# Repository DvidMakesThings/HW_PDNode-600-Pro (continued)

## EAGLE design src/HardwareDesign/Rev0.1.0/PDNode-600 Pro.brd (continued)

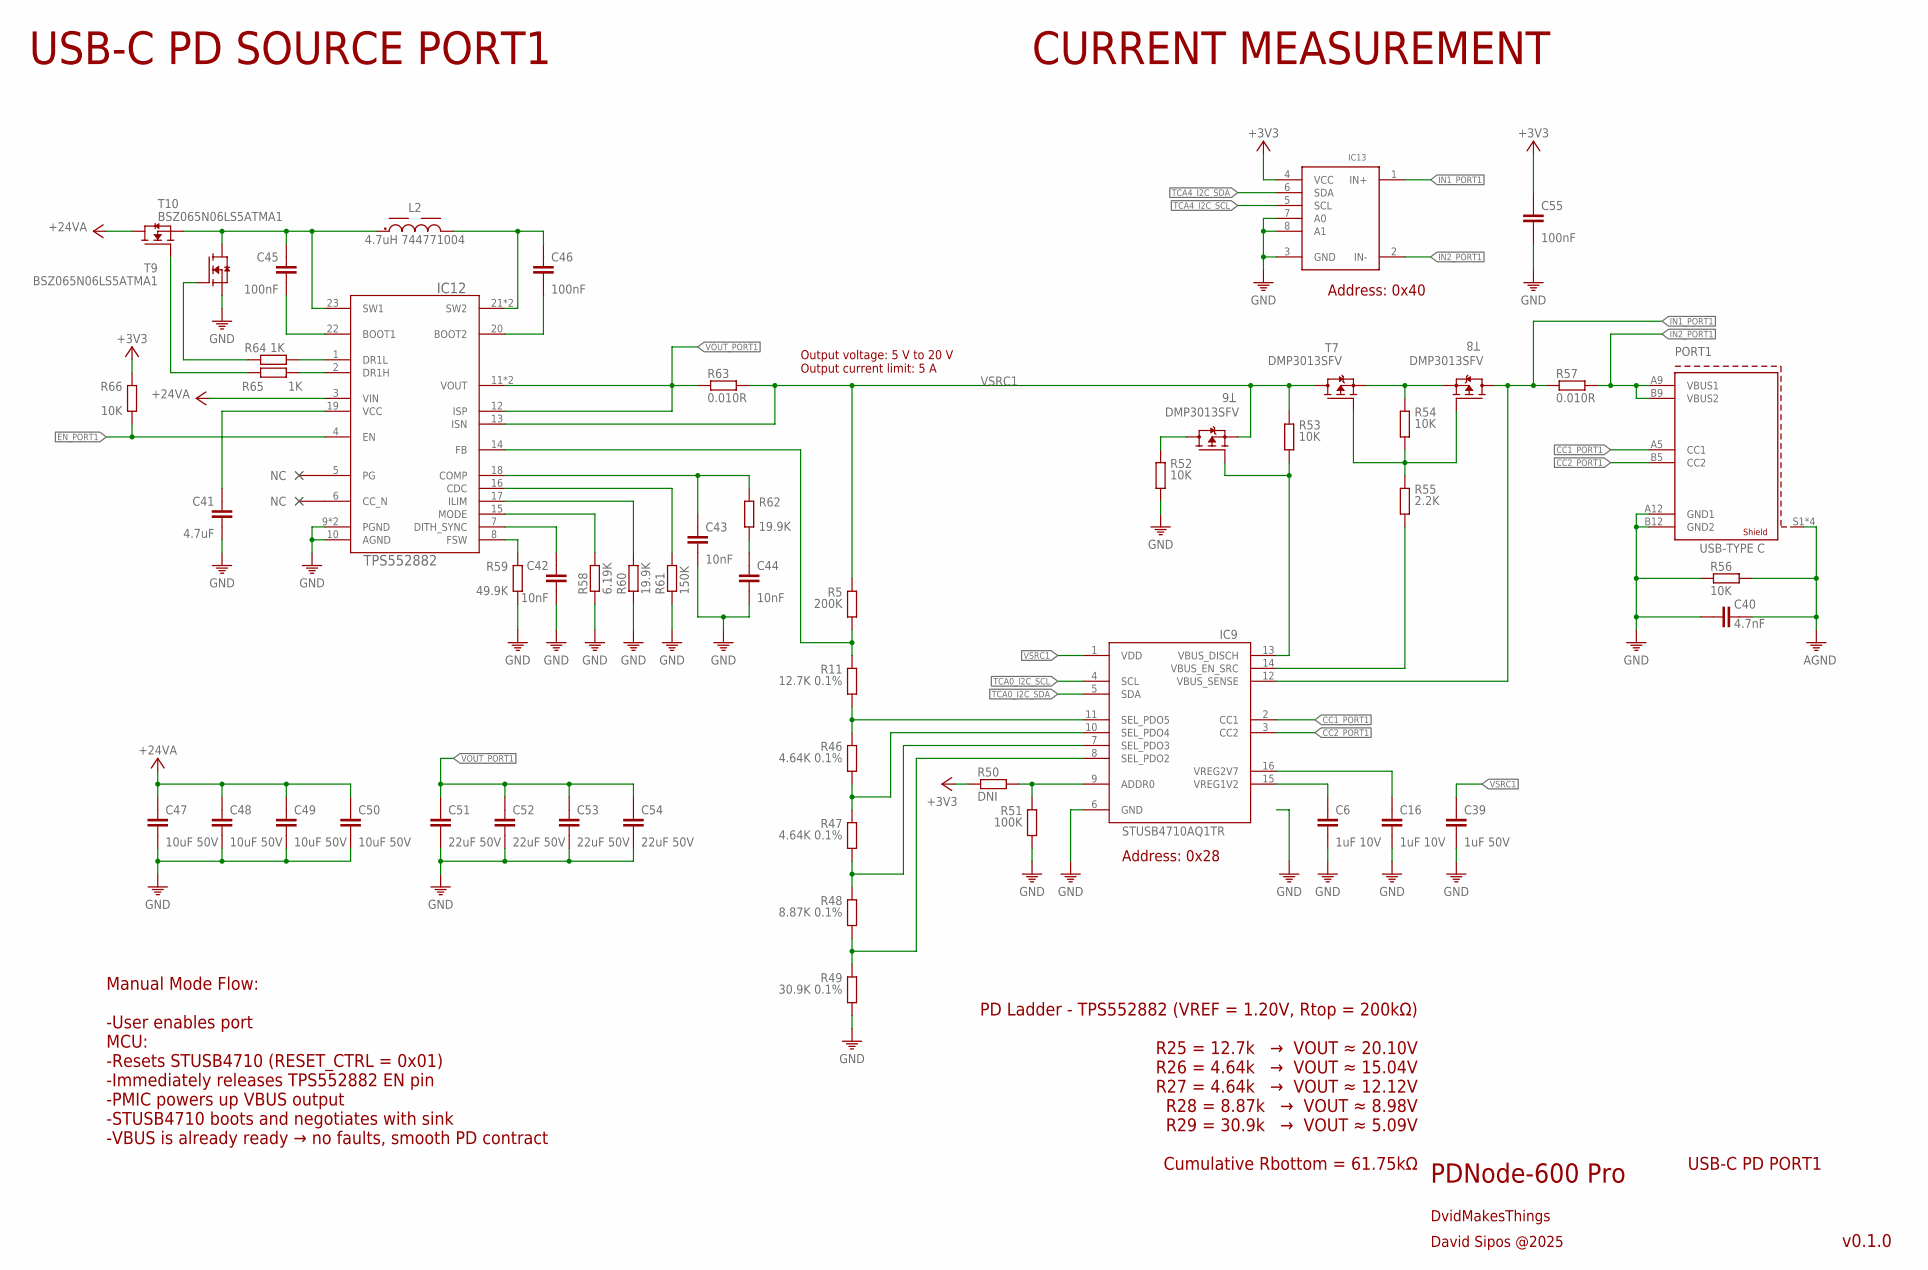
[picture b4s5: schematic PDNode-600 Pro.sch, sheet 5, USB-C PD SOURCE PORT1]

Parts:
C6, C16: 1uF 10V; 0201
C39: 1uF 50V; C0603
C40: 4.7nF; C0402
C41: 4.7uF; C0402
C42, C43, C44: 10nF; 0201
C45, C46: 100nF; C0402
C47, C48, C49, C50: 10uF 50V; C0805
C51, C52, C53, C54: 22uF 50V; C0805
C55: 100nF; 0201
IC9: STUSB4710AQ1TR; QFN50P300X300X55-16N
IC12: TPS552882; RPM0026A-MFG
IC13: INA219BIDCNT; SOT23-8
L2: 4.7uH 744771004; WE-PD_1280
PORT1: 632722100213
R5: 200K; R0201
R11: 12.7K 0.1%; R0201
R46, R47: 4.64K 0.1%; R0201
R48: 8.87K 0.1%; R0201
R49: 30.9K 0.1%; R0201
R50: DNI; R0201
R51: 100K; R0201
R52, R53, R56: 10K; 0402
R54, R66: 10K; R0201
R55: 2.2K; R0201
R57, R63: 0.010R; 2512
R58: 6.19K; R0201
R59: 49.9K; R0201
R60, R62: 19.9K; R0201
R61: 150K; R0201
R64, R65: 1K; R0201
T6, T7, T8: DMP3013SFV; POWERDI3333-8_UX_DIO-L
T9, T10: BSZ065N06LS5ATMA1; POWERDI3333-8_UX_DIO-L

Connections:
+3V3: C55.1, IC13.4 (VCC), R50.1, R66.1; also elsewhere on the board
+24V_A: C47.1, C48.1, C49.1, C50.1, IC12.3 (VIN), T10.5 (D), T10.6 (D), T10.7 (D), T10.8 (D), T10.9 (D); also elsewhere on the board
AGND: C40.2, PORT1.S1 (SHIELD1), PORT1.S2 (SHIELD1), PORT1.S3 (SHIELD1), PORT1.S4 (SHIELD1), R56.2; also elsewhere on the board
CC1_PORT1: IC9.2 (CC1), PORT1.A5 (CC1)
CC2_PORT1: IC9.3 (CC2), PORT1.B5 (CC2)
EN_PORT1: IC12.4 (EN), R66.2; also elsewhere on the board
GND: C6.2, C16.2, C39.2, C40.1, C41.2, C42.2, C43.2, C44.2, C47.2, C48.2, C49.2, C50.2, C51.2, C52.2, C53.2, C54.2, C55.2, IC9.6 (GND), IC12.9 (PGND), IC12.10 (AGND), IC12.24 (PGND), IC13.3 (GND), IC13.7 (A0), IC13.8 (A1), PORT1.A12 (GND1), PORT1.B12 (GND2), R49.2, R51.2, R52.2, R56.1, R58.2, R59.2, R60.2, R61.2, T9.1 (S), T9.2 (S), T9.3 (S); also elsewhere on the board
IN1_PORT1: IC9.12 (VBUS_SENSE), IC13.1 (IN+), R57.1, T8.5 (D), T8.6 (D), T8.7 (D), T8.8 (D), T8.9 (D)
IN2_PORT1: IC13.2 (IN-), PORT1.A9 (VBUS1), PORT1.B9 (VBUS2), R57.2
unnamed: IC12.14 (FB), R5.2, R11.1
unnamed: IC9.11 (SEL_PDO5), R11.2, R46.1
unnamed: IC9.10 (SEL_PDO4), R46.2, R47.1
unnamed: IC9.7 (SEL_PDO3), R47.2, R48.1
unnamed: IC9.8 (SEL_PDO2), R48.2, R49.1
unnamed: C6.1, IC9.15 (VREG1V2)
unnamed: C16.1, IC9.16 (VREG2V7)
unnamed: IC9.9 (ADDR0), R50.2, R51.1
unnamed: R52.1, T6.5 (D), T6.6 (D), T6.7 (D), T6.8 (D), T6.9 (D)
unnamed: IC9.13 (VBUS_DISCH), R53.2, T6.4 (G)
unnamed: R54.1, T7.1 (S), T7.2 (S), T7.3 (S), T8.1 (S), T8.2 (S), T8.3 (S)
unnamed: R54.2, R55.1, T7.4 (G), T8.4 (G)
unnamed: IC9.14 (VBUS_EN_SRC), R55.2
unnamed: C44.1, R62.2
unnamed: IC12.8 (FSW), R59.1
unnamed: C42.1, IC12.7 (DITH_SYNC)
unnamed: IC12.15 (MODE), R58.1
unnamed: IC12.17 (ILIM), R60.1
unnamed: IC12.16 (CDC), R61.1
unnamed: C43.1, IC12.18 (COMP), R62.1
unnamed: C41.1, IC12.19 (VCC)
unnamed: C45.1, IC12.23 (SW1), L2.1, T9.5 (D), T9.6 (D), T9.7 (D), T9.8 (D), T9.9 (D), T10.1 (S), T10.2 (S), T10.3 (S)
unnamed: C46.1, IC12.21 (SW2), IC12.25 (SW2), L2.2
unnamed: C45.2, IC12.22 (BOOT1)
unnamed: C46.2, IC12.20 (BOOT2)
unnamed: R65.2, T10.4 (G)
unnamed: R64.2, T9.4 (G)
unnamed: IC12.1 (DR1L), R64.1
unnamed: IC12.2 (DR1H), R65.1
TCA0_I2C_SCL: IC9.4 (SCL); also elsewhere on the board
TCA0_I2C_SDA: IC9.5 (SDA); also elsewhere on the board
TCA4_I2C_SCL: IC13.5 (SCL); also elsewhere on the board
TCA4_I2C_SDA: IC13.6 (SDA); also elsewhere on the board
VOUT_PORT1: C51.1, C52.1, C53.1, C54.1, IC12.11 (VOUT), IC12.12 (ISP), IC12.26 (VOUT), R63.1
VSRC1: C39.1, IC9.1 (VDD), IC12.13 (ISN), R5.1, R53.1, R63.2, T6.1 (S), T6.2 (S), T6.3 (S), T7.5 (D), T7.6 (D), T7.7 (D), T7.8 (D), T7.9 (D)

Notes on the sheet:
PDNode-600 Pro
DvidMakesThings
David Sipos @2025
USB-C PD SOURCE PORT1
CURRENT MEASUREMENT
USB-C PD PORT1
v0.1.0
Manual Mode Flow: -User enables port MCU: -Resets STUSB4710 (RESET_CTRL = 0x01) -Immediately releases TPS552882 EN pin -PMIC powers up VBUS output -STUSB4710 boots and negotiates with sink -VBUS is already ready → no faults, smooth PD contract
Output voltage: 5 V to 20 V Output current limit: 5 A
PD Ladder - TPS552882 (VREF = 1.20V, Rtop = 200kΩ) R25 = 12.7k → VOUT ≈ 20.10V R26 = 4.64k → VOUT ≈ 15.04V R27 = 4.64k → VOUT ≈ 12.12V R28 = 8.87k → VOUT ≈ 8.98V R29 = 30.9k → VOUT ≈ 5.09V Cumulative Rbottom = 61.75kΩ
Address: 0x40
Address: 0x28

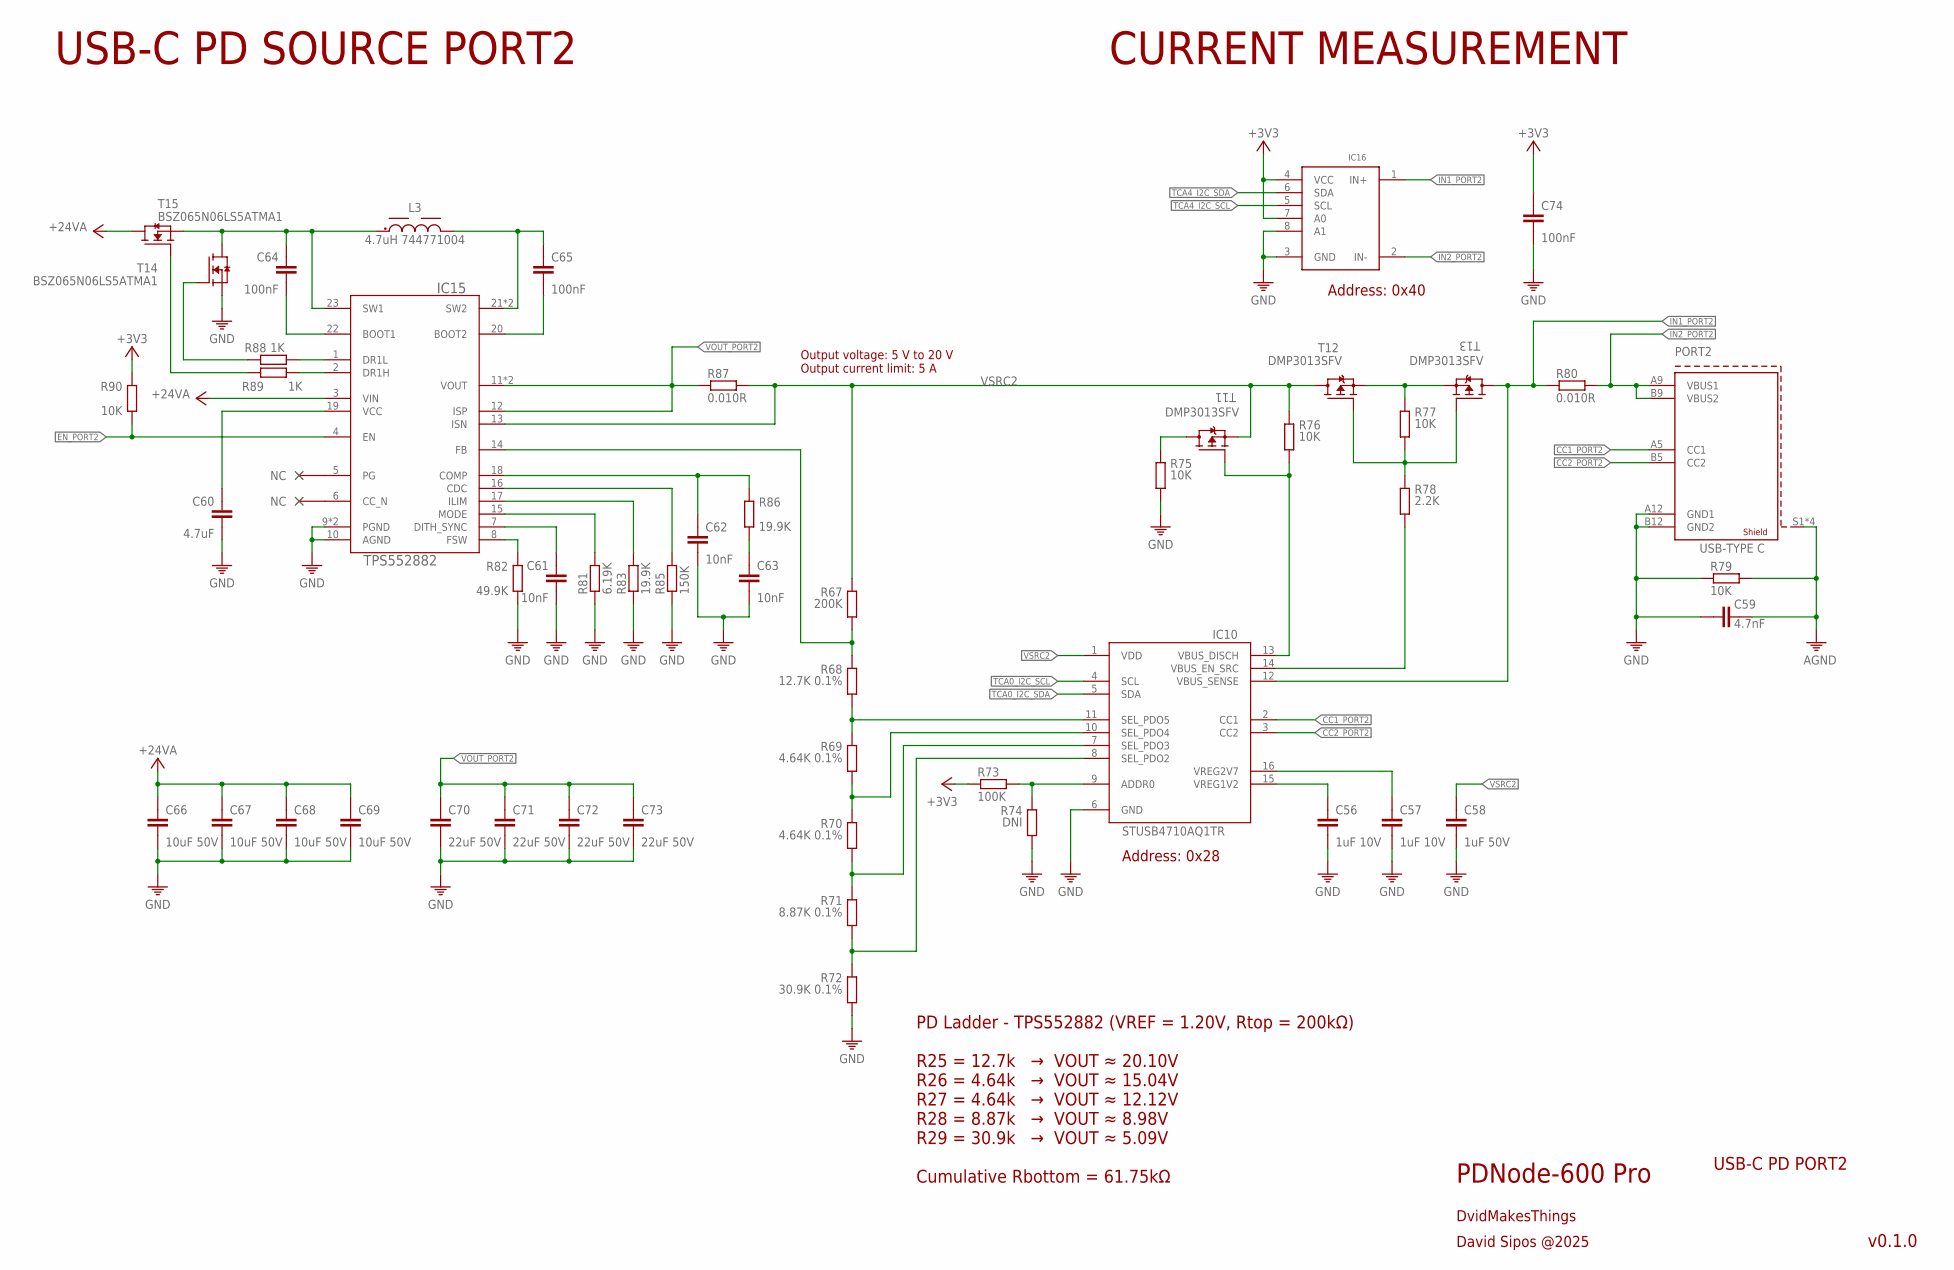
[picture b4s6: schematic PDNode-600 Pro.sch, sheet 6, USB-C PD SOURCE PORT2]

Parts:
C56, C57: 1uF 10V; 0201
C58: 1uF 50V; C0603
C59: 4.7nF; C0402
C60: 4.7uF; C0402
C61, C62, C63: 10nF; 0201
C64, C65: 100nF; C0402
C66, C67, C68, C69: 10uF 50V; C0805
C70, C71, C72, C73: 22uF 50V; C0805
C74: 100nF; 0201
IC10: STUSB4710AQ1TR; QFN50P300X300X55-16N
IC15: TPS552882; RPM0026A-MFG
IC16: INA219BIDCNT; SOT23-8
L3: 4.7uH 744771004; WE-PD_1280
PORT2: 632722100213
R67: 200K; R0201
R68: 12.7K 0.1%; R0201
R69, R70: 4.64K 0.1%; R0201
R71: 8.87K 0.1%; R0201
R72: 30.9K 0.1%; R0201
R73: 100K; R0201
R74: DNI; R0201
R75, R76, R79: 10K; 0402
R77, R90: 10K; R0201
R78: 2.2K; R0201
R80, R87: 0.010R; 2512
R81: 6.19K; R0201
R82: 49.9K; R0201
R83, R86: 19.9K; R0201
R85: 150K; R0201
R88, R89: 1K; R0201
T11, T12, T13: DMP3013SFV; POWERDI3333-8_UX_DIO-L
T14, T15: BSZ065N06LS5ATMA1; POWERDI3333-8_UX_DIO-L

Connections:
+3V3: C74.1, IC16.4 (VCC), IC16.7 (A0), R73.1, R90.1; also elsewhere on the board
+24V_A: C66.1, C67.1, C68.1, C69.1, IC15.3 (VIN), T15.5 (D), T15.6 (D), T15.7 (D), T15.8 (D), T15.9 (D); also elsewhere on the board
AGND: C59.2, PORT2.S1 (SHIELD1), PORT2.S2 (SHIELD1), PORT2.S3 (SHIELD1), PORT2.S4 (SHIELD1), R79.2; also elsewhere on the board
CC1_PORT2: IC10.2 (CC1), PORT2.A5 (CC1)
CC2_PORT2: IC10.3 (CC2), PORT2.B5 (CC2)
EN_PORT2: IC15.4 (EN), R90.2; also elsewhere on the board
GND: C56.2, C57.2, C58.2, C59.1, C60.2, C61.2, C62.2, C63.2, C66.2, C67.2, C68.2, C69.2, C70.2, C71.2, C72.2, C73.2, C74.2, IC10.6 (GND), IC15.9 (PGND), IC15.10 (AGND), IC15.24 (PGND), IC16.3 (GND), IC16.8 (A1), PORT2.A12 (GND1), PORT2.B12 (GND2), R72.2, R74.2, R75.2, R79.1, R81.2, R82.2, R83.2, R85.2, T14.1 (S), T14.2 (S), T14.3 (S); also elsewhere on the board
IN1_PORT2: IC10.12 (VBUS_SENSE), IC16.1 (IN+), R80.1, T13.5 (D), T13.6 (D), T13.7 (D), T13.8 (D), T13.9 (D)
IN2_PORT2: IC16.2 (IN-), PORT2.A9 (VBUS1), PORT2.B9 (VBUS2), R80.2
unnamed: IC15.14 (FB), R67.2, R68.1
unnamed: IC10.11 (SEL_PDO5), R68.2, R69.1
unnamed: IC10.10 (SEL_PDO4), R69.2, R70.1
unnamed: IC10.7 (SEL_PDO3), R70.2, R71.1
unnamed: IC10.8 (SEL_PDO2), R71.2, R72.1
unnamed: C56.1, IC10.15 (VREG1V2)
unnamed: C57.1, IC10.16 (VREG2V7)
unnamed: IC10.9 (ADDR0), R73.2, R74.1
unnamed: R75.1, T11.5 (D), T11.6 (D), T11.7 (D), T11.8 (D), T11.9 (D)
unnamed: IC10.13 (VBUS_DISCH), R76.2, T11.4 (G)
unnamed: R77.1, T12.1 (S), T12.2 (S), T12.3 (S), T13.1 (S), T13.2 (S), T13.3 (S)
unnamed: R77.2, R78.1, T12.4 (G), T13.4 (G)
unnamed: IC10.14 (VBUS_EN_SRC), R78.2
unnamed: C63.1, R86.2
unnamed: IC15.8 (FSW), R82.1
unnamed: C61.1, IC15.7 (DITH_SYNC)
unnamed: IC15.15 (MODE), R81.1
unnamed: IC15.17 (ILIM), R83.1
unnamed: IC15.16 (CDC), R85.1
unnamed: C62.1, IC15.18 (COMP), R86.1
unnamed: C60.1, IC15.19 (VCC)
unnamed: C64.1, IC15.23 (SW1), L3.1, T14.5 (D), T14.6 (D), T14.7 (D), T14.8 (D), T14.9 (D), T15.1 (S), T15.2 (S), T15.3 (S)
unnamed: C65.1, IC15.21 (SW2), IC15.25 (SW2), L3.2
unnamed: C64.2, IC15.22 (BOOT1)
unnamed: C65.2, IC15.20 (BOOT2)
unnamed: R89.2, T15.4 (G)
unnamed: R88.2, T14.4 (G)
unnamed: IC15.1 (DR1L), R88.1
unnamed: IC15.2 (DR1H), R89.1
TCA0_I2C_SCL: IC10.4 (SCL); also elsewhere on the board
TCA0_I2C_SDA: IC10.5 (SDA); also elsewhere on the board
TCA4_I2C_SCL: IC16.5 (SCL); also elsewhere on the board
TCA4_I2C_SDA: IC16.6 (SDA); also elsewhere on the board
VOUT_PORT2: C70.1, C71.1, C72.1, C73.1, IC15.11 (VOUT), IC15.12 (ISP), IC15.26 (VOUT), R87.1
VSRC2: C58.1, IC10.1 (VDD), IC15.13 (ISN), R67.1, R76.1, R87.2, T11.1 (S), T11.2 (S), T11.3 (S), T12.5 (D), T12.6 (D), T12.7 (D), T12.8 (D), T12.9 (D)

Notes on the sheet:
PDNode-600 Pro
DvidMakesThings
David Sipos @2025
USB-C PD SOURCE PORT2
CURRENT MEASUREMENT
USB-C PD PORT2
v0.1.0
Output voltage: 5 V to 20 V Output current limit: 5 A
PD Ladder - TPS552882 (VREF = 1.20V, Rtop = 200kΩ) R25 = 12.7k → VOUT ≈ 20.10V R26 = 4.64k → VOUT ≈ 15.04V R27 = 4.64k → VOUT ≈ 12.12V R28 = 8.87k → VOUT ≈ 8.98V R29 = 30.9k → VOUT ≈ 5.09V Cumulative Rbottom = 61.75kΩ
Address: 0x40
Address: 0x28

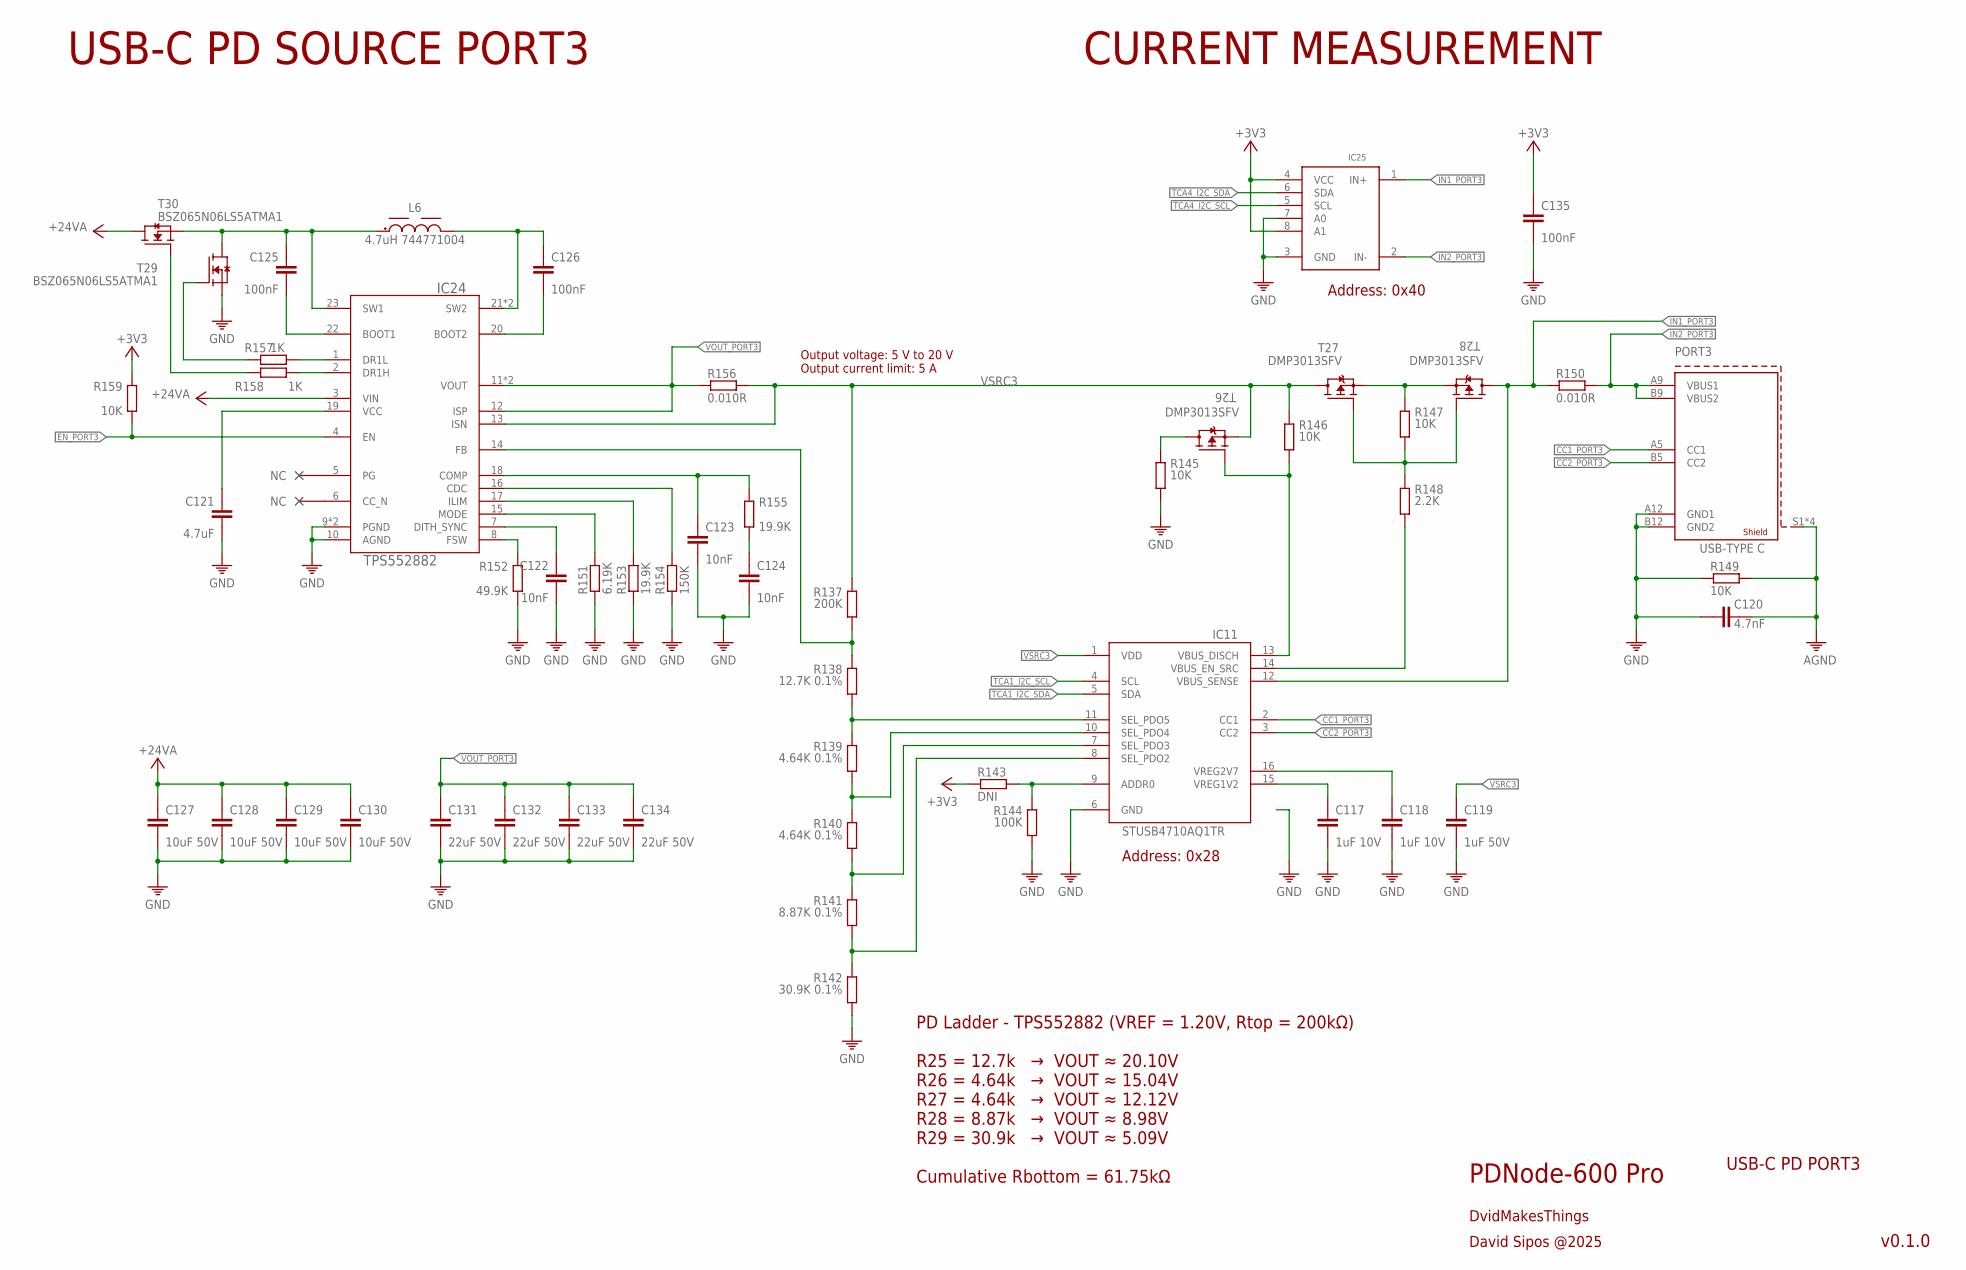
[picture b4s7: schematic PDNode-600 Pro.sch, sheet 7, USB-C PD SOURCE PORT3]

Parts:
C117, C118: 1uF 10V; 0201
C119: 1uF 50V; C0603
C120: 4.7nF; C0402
C121: 4.7uF; C0402
C122, C123, C124: 10nF; 0201
C125, C126: 100nF; C0402
C127, C128, C129, C130: 10uF 50V; C0805
C131, C132, C133, C134: 22uF 50V; C0805
C135: 100nF; 0201
IC11: STUSB4710AQ1TR; QFN50P300X300X55-16N
IC24: TPS552882; RPM0026A-MFG
IC25: INA219BIDCNT; SOT23-8
L6: 4.7uH 744771004; WE-PD_1280
PORT3: 632722100213
R137: 200K; R0201
R138: 12.7K 0.1%; R0201
R139, R140: 4.64K 0.1%; R0201
R141: 8.87K 0.1%; R0201
R142: 30.9K 0.1%; R0201
R143: DNI; R0201
R144: 100K; R0201
R145, R146, R149: 10K; 0402
R147, R159: 10K; R0201
R148: 2.2K; R0201
R150, R156: 0.010R; 2512
R151: 6.19K; R0201
R152: 49.9K; R0201
R153, R155: 19.9K; R0201
R154: 150K; R0201
R157, R158: 1K; R0201
T26, T27, T28: DMP3013SFV; POWERDI3333-8_UX_DIO-L
T29, T30: BSZ065N06LS5ATMA1; POWERDI3333-8_UX_DIO-L

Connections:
+3V3: C135.1, IC25.4 (VCC), IC25.8 (A1), R143.1, R159.1; also elsewhere on the board
+24V_A: C127.1, C128.1, C129.1, C130.1, IC24.3 (VIN), T30.5 (D), T30.6 (D), T30.7 (D), T30.8 (D), T30.9 (D); also elsewhere on the board
AGND: C120.2, PORT3.S1 (SHIELD1), PORT3.S2 (SHIELD1), PORT3.S3 (SHIELD1), PORT3.S4 (SHIELD1), R149.2; also elsewhere on the board
CC1_PORT3: IC11.2 (CC1), PORT3.A5 (CC1)
CC2_PORT3: IC11.3 (CC2), PORT3.B5 (CC2)
EN_PORT3: IC24.4 (EN), R159.2; also elsewhere on the board
GND: C117.2, C118.2, C119.2, C120.1, C121.2, C122.2, C123.2, C124.2, C127.2, C128.2, C129.2, C130.2, C131.2, C132.2, C133.2, C134.2, C135.2, IC11.6 (GND), IC24.9 (PGND), IC24.10 (AGND), IC24.24 (PGND), IC25.3 (GND), IC25.7 (A0), PORT3.A12 (GND1), PORT3.B12 (GND2), R142.2, R144.2, R145.2, R149.1, R151.2, R152.2, R153.2, R154.2, T29.1 (S), T29.2 (S), T29.3 (S); also elsewhere on the board
IN1_PORT3: IC11.12 (VBUS_SENSE), IC25.1 (IN+), R150.1, T28.5 (D), T28.6 (D), T28.7 (D), T28.8 (D), T28.9 (D)
IN2_PORT3: IC25.2 (IN-), PORT3.A9 (VBUS1), PORT3.B9 (VBUS2), R150.2
unnamed: IC24.14 (FB), R137.2, R138.1
unnamed: IC11.11 (SEL_PDO5), R138.2, R139.1
unnamed: IC11.10 (SEL_PDO4), R139.2, R140.1
unnamed: IC11.7 (SEL_PDO3), R140.2, R141.1
unnamed: IC11.8 (SEL_PDO2), R141.2, R142.1
unnamed: C117.1, IC11.15 (VREG1V2)
unnamed: C118.1, IC11.16 (VREG2V7)
unnamed: IC11.9 (ADDR0), R143.2, R144.1
unnamed: R145.1, T26.5 (D), T26.6 (D), T26.7 (D), T26.8 (D), T26.9 (D)
unnamed: IC11.13 (VBUS_DISCH), R146.2, T26.4 (G)
unnamed: R147.1, T27.1 (S), T27.2 (S), T27.3 (S), T28.1 (S), T28.2 (S), T28.3 (S)
unnamed: R147.2, R148.1, T27.4 (G), T28.4 (G)
unnamed: IC11.14 (VBUS_EN_SRC), R148.2
unnamed: C124.1, R155.2
unnamed: IC24.8 (FSW), R152.1
unnamed: C122.1, IC24.7 (DITH_SYNC)
unnamed: IC24.15 (MODE), R151.1
unnamed: IC24.17 (ILIM), R153.1
unnamed: IC24.16 (CDC), R154.1
unnamed: C123.1, IC24.18 (COMP), R155.1
unnamed: C121.1, IC24.19 (VCC)
unnamed: C125.1, IC24.23 (SW1), L6.1, T29.5 (D), T29.6 (D), T29.7 (D), T29.8 (D), T29.9 (D), T30.1 (S), T30.2 (S), T30.3 (S)
unnamed: C126.1, IC24.21 (SW2), IC24.25 (SW2), L6.2
unnamed: C125.2, IC24.22 (BOOT1)
unnamed: C126.2, IC24.20 (BOOT2)
unnamed: R158.2, T30.4 (G)
unnamed: R157.2, T29.4 (G)
unnamed: IC24.1 (DR1L), R157.1
unnamed: IC24.2 (DR1H), R158.1
TCA1_I2C_SCL: IC11.4 (SCL); also elsewhere on the board
TCA1_I2C_SDA: IC11.5 (SDA); also elsewhere on the board
TCA4_I2C_SCL: IC25.5 (SCL); also elsewhere on the board
TCA4_I2C_SDA: IC25.6 (SDA); also elsewhere on the board
VOUT_PORT3: C131.1, C132.1, C133.1, C134.1, IC24.11 (VOUT), IC24.12 (ISP), IC24.26 (VOUT), R156.1
VSRC3: C119.1, IC11.1 (VDD), IC24.13 (ISN), R137.1, R146.1, R156.2, T26.1 (S), T26.2 (S), T26.3 (S), T27.5 (D), T27.6 (D), T27.7 (D), T27.8 (D), T27.9 (D)

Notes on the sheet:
PDNode-600 Pro
DvidMakesThings
David Sipos @2025
USB-C PD SOURCE PORT3
CURRENT MEASUREMENT
USB-C PD PORT3
v0.1.0
Output voltage: 5 V to 20 V Output current limit: 5 A
PD Ladder - TPS552882 (VREF = 1.20V, Rtop = 200kΩ) R25 = 12.7k → VOUT ≈ 20.10V R26 = 4.64k → VOUT ≈ 15.04V R27 = 4.64k → VOUT ≈ 12.12V R28 = 8.87k → VOUT ≈ 8.98V R29 = 30.9k → VOUT ≈ 5.09V Cumulative Rbottom = 61.75kΩ
Address: 0x40
Address: 0x28

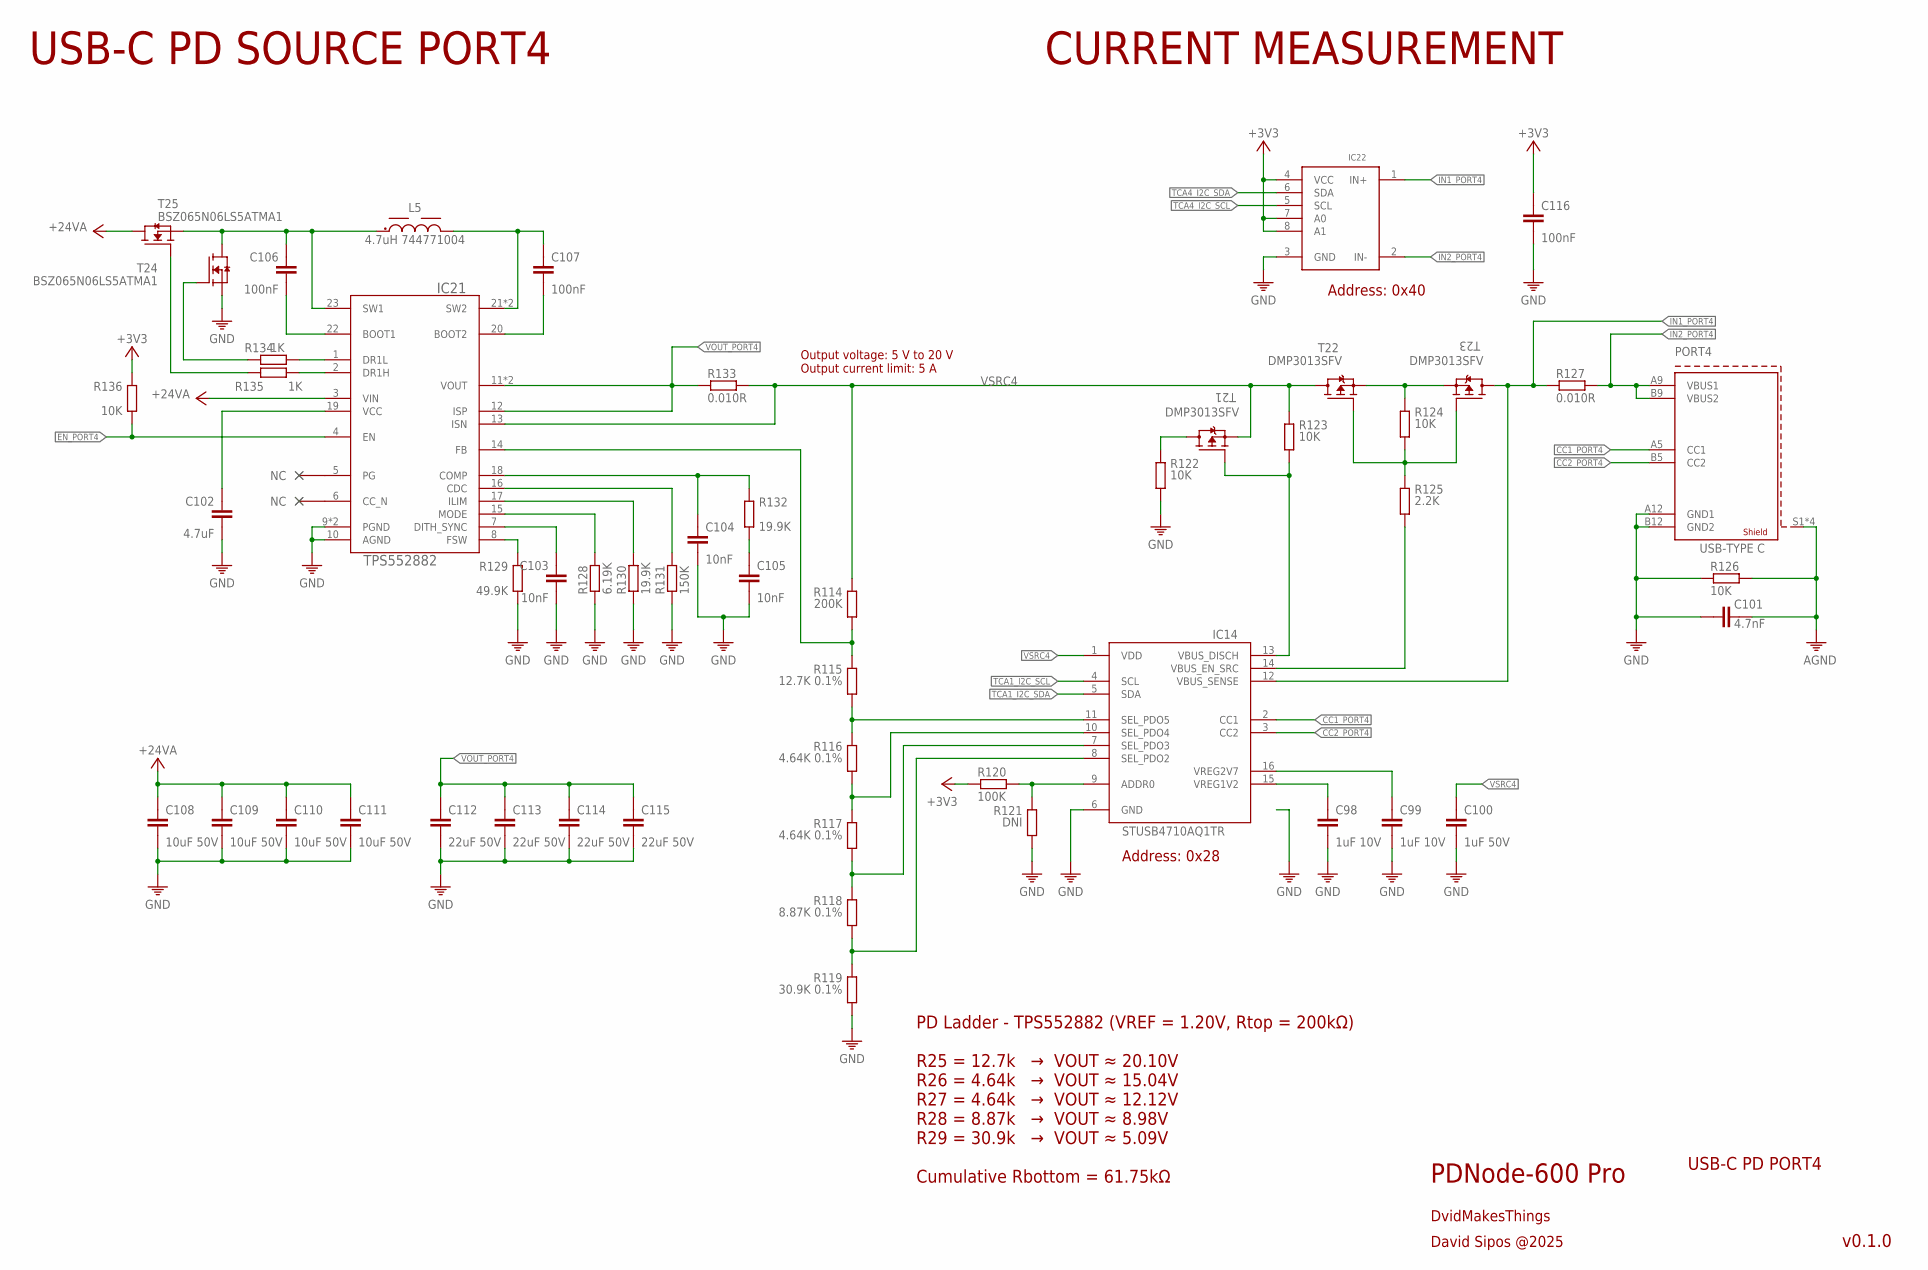
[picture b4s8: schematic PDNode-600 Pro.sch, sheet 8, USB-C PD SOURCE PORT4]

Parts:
C98, C99: 1uF 10V; 0201
C100: 1uF 50V; C0603
C101: 4.7nF; C0402
C102: 4.7uF; C0402
C103, C104, C105: 10nF; 0201
C106, C107: 100nF; C0402
C108, C109, C110, C111: 10uF 50V; C0805
C112, C113, C114, C115: 22uF 50V; C0805
C116: 100nF; 0201
IC14: STUSB4710AQ1TR; QFN50P300X300X55-16N
IC21: TPS552882; RPM0026A-MFG
IC22: INA219BIDCNT; SOT23-8
L5: 4.7uH 744771004; WE-PD_1280
PORT4: 632722100213
R114: 200K; R0201
R115: 12.7K 0.1%; R0201
R116, R117: 4.64K 0.1%; R0201
R118: 8.87K 0.1%; R0201
R119: 30.9K 0.1%; R0201
R120: 100K; R0201
R121: DNI; R0201
R122, R123, R126: 10K; 0402
R124, R136: 10K; R0201
R125: 2.2K; R0201
R127, R133: 0.010R; 2512
R128: 6.19K; R0201
R129: 49.9K; R0201
R130, R132: 19.9K; R0201
R131: 150K; R0201
R134, R135: 1K; R0201
T21, T22, T23: DMP3013SFV; POWERDI3333-8_UX_DIO-L
T24, T25: BSZ065N06LS5ATMA1; POWERDI3333-8_UX_DIO-L

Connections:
+3V3: C116.1, IC22.4 (VCC), IC22.7 (A0), IC22.8 (A1), R120.1, R136.1; also elsewhere on the board
+24V_A: C108.1, C109.1, C110.1, C111.1, IC21.3 (VIN), T25.5 (D), T25.6 (D), T25.7 (D), T25.8 (D), T25.9 (D); also elsewhere on the board
AGND: C101.2, PORT4.S1 (SHIELD1), PORT4.S2 (SHIELD1), PORT4.S3 (SHIELD1), PORT4.S4 (SHIELD1), R126.2; also elsewhere on the board
CC1_PORT4: IC14.2 (CC1), PORT4.A5 (CC1)
CC2_PORT4: IC14.3 (CC2), PORT4.B5 (CC2)
EN_PORT4: IC21.4 (EN), R136.2; also elsewhere on the board
GND: C98.2, C99.2, C100.2, C101.1, C102.2, C103.2, C104.2, C105.2, C108.2, C109.2, C110.2, C111.2, C112.2, C113.2, C114.2, C115.2, C116.2, IC14.6 (GND), IC21.9 (PGND), IC21.10 (AGND), IC21.24 (PGND), IC22.3 (GND), PORT4.A12 (GND1), PORT4.B12 (GND2), R119.2, R121.2, R122.2, R126.1, R128.2, R129.2, R130.2, R131.2, T24.1 (S), T24.2 (S), T24.3 (S); also elsewhere on the board
IN1_PORT4: IC14.12 (VBUS_SENSE), IC22.1 (IN+), R127.1, T23.5 (D), T23.6 (D), T23.7 (D), T23.8 (D), T23.9 (D)
IN2_PORT4: IC22.2 (IN-), PORT4.A9 (VBUS1), PORT4.B9 (VBUS2), R127.2
unnamed: IC21.14 (FB), R114.2, R115.1
unnamed: IC14.11 (SEL_PDO5), R115.2, R116.1
unnamed: IC14.10 (SEL_PDO4), R116.2, R117.1
unnamed: IC14.7 (SEL_PDO3), R117.2, R118.1
unnamed: IC14.8 (SEL_PDO2), R118.2, R119.1
unnamed: C98.1, IC14.15 (VREG1V2)
unnamed: C99.1, IC14.16 (VREG2V7)
unnamed: IC14.9 (ADDR0), R120.2, R121.1
unnamed: R122.1, T21.5 (D), T21.6 (D), T21.7 (D), T21.8 (D), T21.9 (D)
unnamed: IC14.13 (VBUS_DISCH), R123.2, T21.4 (G)
unnamed: R124.1, T22.1 (S), T22.2 (S), T22.3 (S), T23.1 (S), T23.2 (S), T23.3 (S)
unnamed: R124.2, R125.1, T22.4 (G), T23.4 (G)
unnamed: IC14.14 (VBUS_EN_SRC), R125.2
unnamed: C105.1, R132.2
unnamed: IC21.8 (FSW), R129.1
unnamed: C103.1, IC21.7 (DITH_SYNC)
unnamed: IC21.15 (MODE), R128.1
unnamed: IC21.17 (ILIM), R130.1
unnamed: IC21.16 (CDC), R131.1
unnamed: C104.1, IC21.18 (COMP), R132.1
unnamed: C102.1, IC21.19 (VCC)
unnamed: C106.1, IC21.23 (SW1), L5.1, T24.5 (D), T24.6 (D), T24.7 (D), T24.8 (D), T24.9 (D), T25.1 (S), T25.2 (S), T25.3 (S)
unnamed: C107.1, IC21.21 (SW2), IC21.25 (SW2), L5.2
unnamed: C106.2, IC21.22 (BOOT1)
unnamed: C107.2, IC21.20 (BOOT2)
unnamed: R135.2, T25.4 (G)
unnamed: R134.2, T24.4 (G)
unnamed: IC21.1 (DR1L), R134.1
unnamed: IC21.2 (DR1H), R135.1
TCA1_I2C_SCL: IC14.4 (SCL); also elsewhere on the board
TCA1_I2C_SDA: IC14.5 (SDA); also elsewhere on the board
TCA4_I2C_SCL: IC22.5 (SCL); also elsewhere on the board
TCA4_I2C_SDA: IC22.6 (SDA); also elsewhere on the board
VOUT_PORT4: C112.1, C113.1, C114.1, C115.1, IC21.11 (VOUT), IC21.12 (ISP), IC21.26 (VOUT), R133.1
VSRC4: C100.1, IC14.1 (VDD), IC21.13 (ISN), R114.1, R123.1, R133.2, T21.1 (S), T21.2 (S), T21.3 (S), T22.5 (D), T22.6 (D), T22.7 (D), T22.8 (D), T22.9 (D)

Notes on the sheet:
PDNode-600 Pro
DvidMakesThings
David Sipos @2025
USB-C PD SOURCE PORT4
CURRENT MEASUREMENT
USB-C PD PORT4
v0.1.0
Output voltage: 5 V to 20 V Output current limit: 5 A
PD Ladder - TPS552882 (VREF = 1.20V, Rtop = 200kΩ) R25 = 12.7k → VOUT ≈ 20.10V R26 = 4.64k → VOUT ≈ 15.04V R27 = 4.64k → VOUT ≈ 12.12V R28 = 8.87k → VOUT ≈ 8.98V R29 = 30.9k → VOUT ≈ 5.09V Cumulative Rbottom = 61.75kΩ
Address: 0x40
Address: 0x28

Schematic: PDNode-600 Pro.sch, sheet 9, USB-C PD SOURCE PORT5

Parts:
C75, C76: 1uF 10V; 0201
C77: 1uF 50V; C0603
C78: 4.7nF; C0402
C79: 4.7uF; C0402
C80, C81, C86: 10nF; 0201
C87, C88: 100nF; C0402
C89, C90, C91, C92: 10uF 50V; C0805
C93, C94, C95, C96: 22uF 50V; C0805
C97: 100nF; 0201
IC17: STUSB4710AQ1TR; QFN50P300X300X55-16N
IC18: TPS552882; RPM0026A-MFG
IC19: INA219BIDCNT; SOT23-8
L4: 4.7uH 744771004; WE-PD_1280
PORT5: 632722100213
R91: 200K; R0201
R92: 12.7K 0.1%; R0201
R93, R94: 4.64K 0.1%; R0201
R95: 8.87K 0.1%; R0201
R96: 30.9K 0.1%; R0201
R97: DNI; R0201
R98: 100K; R0201
R99, R100, R103: 10K; 0402
R101, R113: 10K; R0201
R102: 2.2K; R0201
R104, R110: 0.010R; 2512
R105: 6.19K; R0201
R106: 49.9K; R0201
R107, R109: 19.9K; R0201
R108: 150K; R0201
R111, R112: 1K; R0201
T16, T17, T18: DMP3013SFV; POWERDI3333-8_UX_DIO-L
T19, T20: BSZ065N06LS5ATMA1; POWERDI3333-8_UX_DIO-L

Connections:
+3V3: C97.1, IC19.4 (VCC), R97.1, R113.1; also elsewhere on the board
+24V_B: C89.1, C90.1, C91.1, C92.1, IC18.3 (VIN), T20.5 (D), T20.6 (D), T20.7 (D), T20.8 (D), T20.9 (D); also elsewhere on the board
AGND: C78.2, PORT5.S1 (SHIELD1), PORT5.S2 (SHIELD1), PORT5.S3 (SHIELD1), PORT5.S4 (SHIELD1), R103.2; also elsewhere on the board
CC1_PORT5: IC17.2 (CC1), PORT5.A5 (CC1)
CC2_PORT5: IC17.3 (CC2), PORT5.B5 (CC2)
EN_PORT5: IC18.4 (EN), R113.2; also elsewhere on the board
GND: C75.2, C76.2, C77.2, C78.1, C79.2, C80.2, C81.2, C86.2, C89.2, C90.2, C91.2, C92.2, C93.2, C94.2, C95.2, C96.2, C97.2, IC17.6 (GND), IC18.9 (PGND), IC18.10 (AGND), IC18.24 (PGND), IC19.3 (GND), IC19.7 (A0), IC19.8 (A1), PORT5.A12 (GND1), PORT5.B12 (GND2), R96.2, R98.2, R99.2, R103.1, R105.2, R106.2, R107.2, R108.2, T19.1 (S), T19.2 (S), T19.3 (S); also elsewhere on the board
IN1_PORT5: IC17.12 (VBUS_SENSE), IC19.1 (IN+), R104.1, T18.5 (D), T18.6 (D), T18.7 (D), T18.8 (D), T18.9 (D)
IN2_PORT5: IC19.2 (IN-), PORT5.A9 (VBUS1), PORT5.B9 (VBUS2), R104.2
unnamed: IC18.14 (FB), R91.2, R92.1
unnamed: IC17.11 (SEL_PDO5), R92.2, R93.1
unnamed: IC17.10 (SEL_PDO4), R93.2, R94.1
unnamed: IC17.7 (SEL_PDO3), R94.2, R95.1
unnamed: IC17.8 (SEL_PDO2), R95.2, R96.1
unnamed: C75.1, IC17.15 (VREG1V2)
unnamed: C76.1, IC17.16 (VREG2V7)
unnamed: IC17.9 (ADDR0), R97.2, R98.1
unnamed: R99.1, T16.5 (D), T16.6 (D), T16.7 (D), T16.8 (D), T16.9 (D)
unnamed: IC17.13 (VBUS_DISCH), R100.2, T16.4 (G)
unnamed: R101.1, T17.1 (S), T17.2 (S), T17.3 (S), T18.1 (S), T18.2 (S), T18.3 (S)
unnamed: R101.2, R102.1, T17.4 (G), T18.4 (G)
unnamed: IC17.14 (VBUS_EN_SRC), R102.2
unnamed: C86.1, R109.2
unnamed: IC18.8 (FSW), R106.1
unnamed: C80.1, IC18.7 (DITH_SYNC)
unnamed: IC18.15 (MODE), R105.1
unnamed: IC18.17 (ILIM), R107.1
unnamed: IC18.16 (CDC), R108.1
unnamed: C81.1, IC18.18 (COMP), R109.1
unnamed: C79.1, IC18.19 (VCC)
unnamed: C87.1, IC18.23 (SW1), L4.1, T19.5 (D), T19.6 (D), T19.7 (D), T19.8 (D), T19.9 (D), T20.1 (S), T20.2 (S), T20.3 (S)
unnamed: C88.1, IC18.21 (SW2), IC18.25 (SW2), L4.2
unnamed: C87.2, IC18.22 (BOOT1)
unnamed: C88.2, IC18.20 (BOOT2)
unnamed: R112.2, T20.4 (G)
unnamed: R111.2, T19.4 (G)
unnamed: IC18.1 (DR1L), R111.1
unnamed: IC18.2 (DR1H), R112.1
TCA2_I2C_SCL: IC17.4 (SCL); also elsewhere on the board
TCA2_I2C_SDA: IC17.5 (SDA); also elsewhere on the board
TCA5_I2C_SCL: IC19.5 (SCL); also elsewhere on the board
TCA5_I2C_SDA: IC19.6 (SDA); also elsewhere on the board
VOUT_PORT5: C93.1, C94.1, C95.1, C96.1, IC18.11 (VOUT), IC18.12 (ISP), IC18.26 (VOUT), R110.1
VSRC5: C77.1, IC17.1 (VDD), IC18.13 (ISN), R91.1, R100.1, R110.2, T16.1 (S), T16.2 (S), T16.3 (S), T17.5 (D), T17.6 (D), T17.7 (D), T17.8 (D), T17.9 (D)

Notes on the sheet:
PDNode-600 Pro
DvidMakesThings
David Sipos @2025
USB-C PD SOURCE PORT5
CURRENT MEASUREMENT
USB-C PD PORT5
v0.1.0
Output voltage: 5 V to 20 V Output current limit: 5 A
PD Ladder - TPS552882 (VREF = 1.20V, Rtop = 200kΩ) R25 = 12.7k → VOUT ≈ 20.10V R26 = 4.64k → VOUT ≈ 15.04V R27 = 4.64k → VOUT ≈ 12.12V R28 = 8.87k → VOUT ≈ 8.98V R29 = 30.9k → VOUT ≈ 5.09V Cumulative Rbottom = 61.75kΩ
Address: 0x40
Address: 0x28
